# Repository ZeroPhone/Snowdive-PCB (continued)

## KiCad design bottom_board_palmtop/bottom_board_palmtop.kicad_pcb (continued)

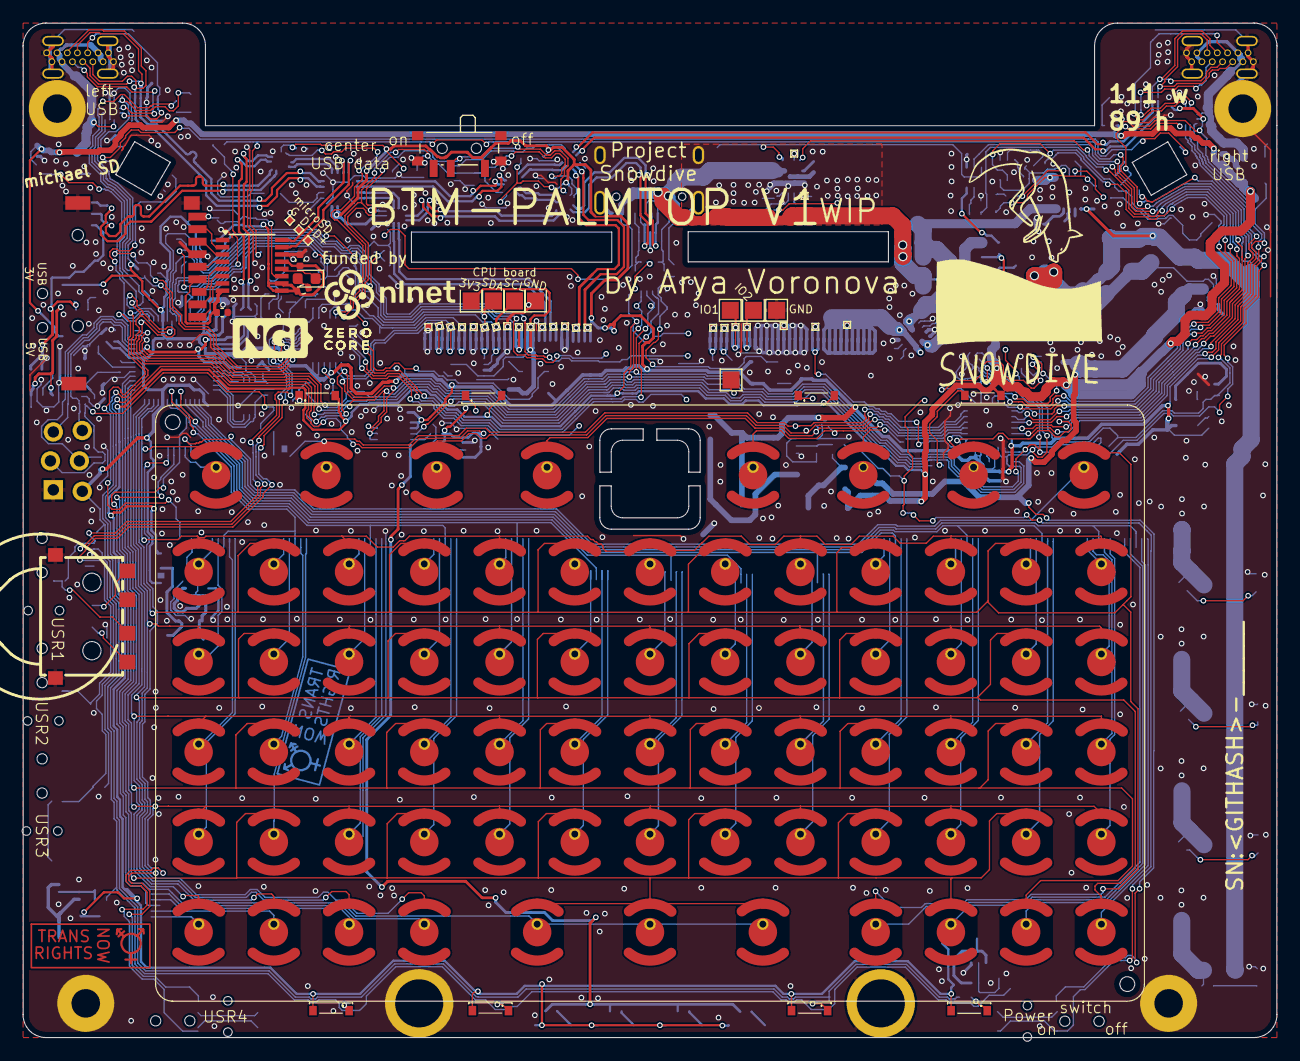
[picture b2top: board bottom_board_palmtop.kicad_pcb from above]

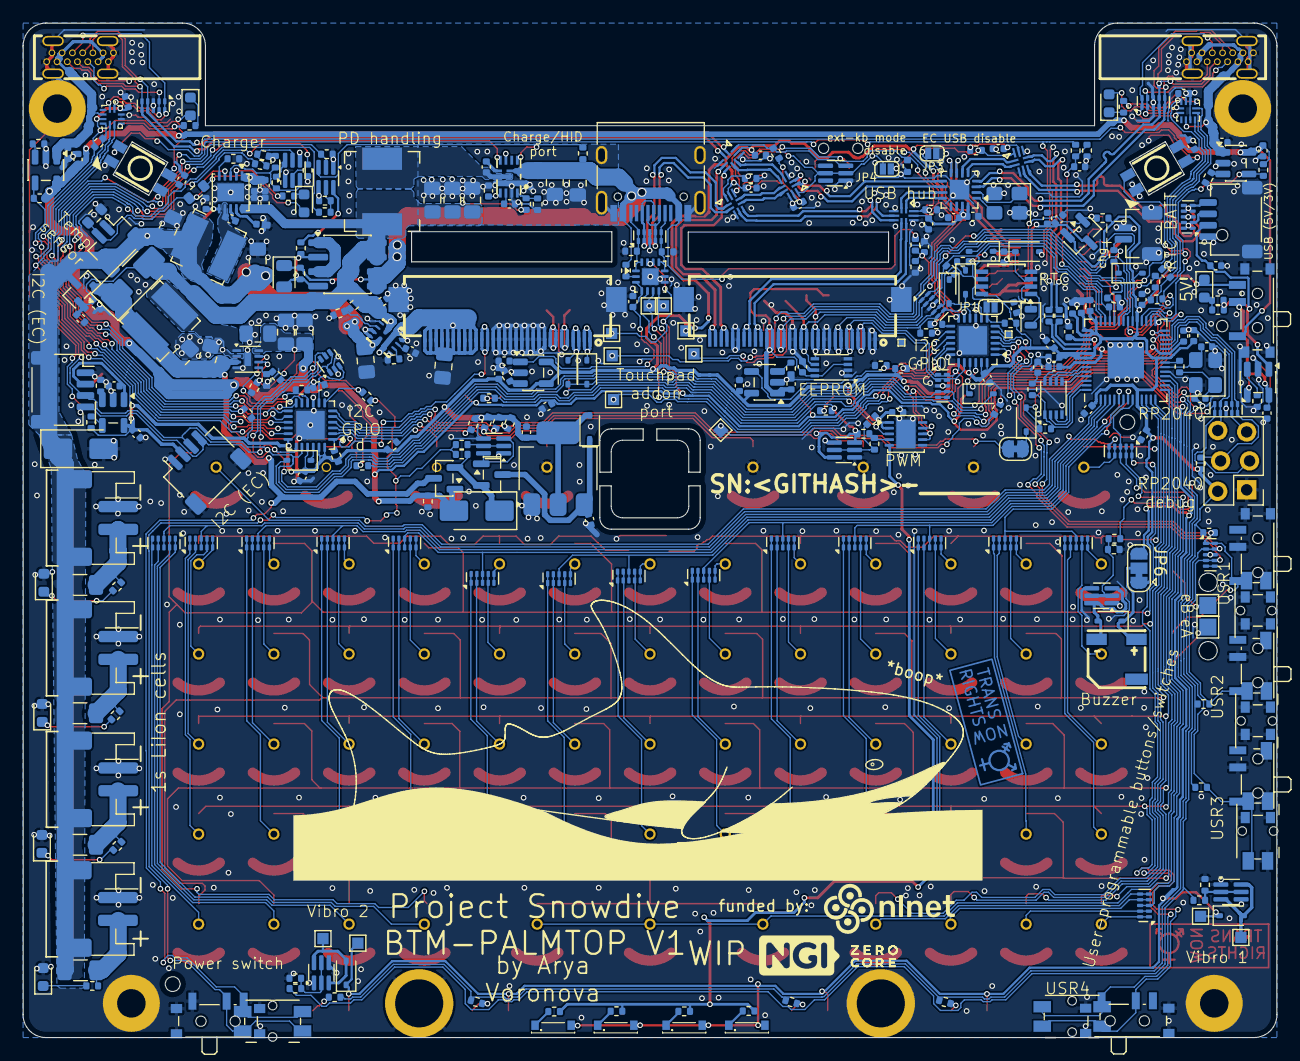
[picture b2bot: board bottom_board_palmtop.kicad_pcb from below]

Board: 2 copper layers, 110.0 x 89.0 mm, 405 parts (347 on the bottom side), 303 nets.

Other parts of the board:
TRNSRTS: Trans Rights now Front
TRNSRTS#2: Trans Rights now Back

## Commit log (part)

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2026-04-04 top_pizero: clarifying the schematic, improving TODO after bringup
2026-05-20 bottom_board_palmtop: boards as-ordered (with a bit of feedback added in sch todo)
2026-05-20 top_board_pizero: added more post-bringup info into TODO; minor changes
2026-06-08 bottom_board_palmtop: v1 almost done
2026-06-10 bottom_board_palmtop: pre-review
2026-06-27 bottom_board_palmtop: more pre-review work
2026-06-28 bottom_board_palmtop: small fixes under U47
